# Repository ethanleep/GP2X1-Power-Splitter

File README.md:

# GP2X1 Power Splitter

These are the board files for an RF power splitter based on the Mini-Circuits GP2X1+ power splitter IC. It can handle up to 1.5W between a frequency range of 2900 - 6200 MHz. It has tested and verified to work but I cannot guarantee performance characteristics because I simply dont have the tools to test it. The boards are 4 layer FR408 PCBs ordered from OSH Park due to the decent RF performance and cost. The SMA footprints on the board are based off of Molex connectors but they work fine with other brands even if the sizes dont match. The boards are uploaded to the OSH Park website and can be viewed and ordered below.

GP2X1+ Data Sheet: https://www.minicircuits.com/pdfs/GP2X+.pdf

OSH Park PCB link:
<a href="https://oshpark.com/shared_projects/WrkGxE40"></img></a>

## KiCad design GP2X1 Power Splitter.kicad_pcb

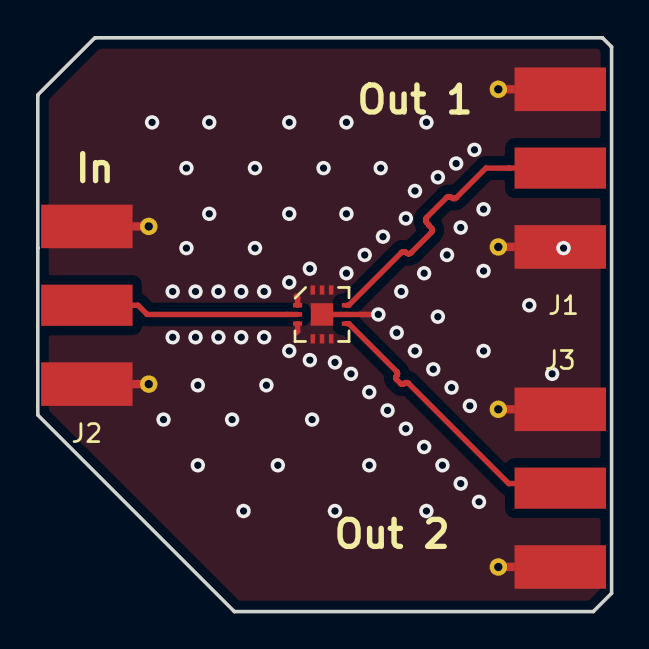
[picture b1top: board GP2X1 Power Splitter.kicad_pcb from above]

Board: 4 copper layers, 31.9 x 31.9 mm, 4 parts (0 on the bottom side), 4 nets.

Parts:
J1, J2, J3: Conn_Coaxial; Molex_SMA_Jack_Edge_Mount
U1: GP2X+; DQ1225

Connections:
GND: J1.2, J2.2, J3.2, U1.1, U1.3, U1.4, U1.5, U1.6, U1.8, U1.10, U1.11, U1.12, U1.EP
unnamed: J1.1, U1.9
unnamed: J2.1, U1.2
unnamed: J3.1, U1.7

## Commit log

2019-05-25 Added board files for splitter
